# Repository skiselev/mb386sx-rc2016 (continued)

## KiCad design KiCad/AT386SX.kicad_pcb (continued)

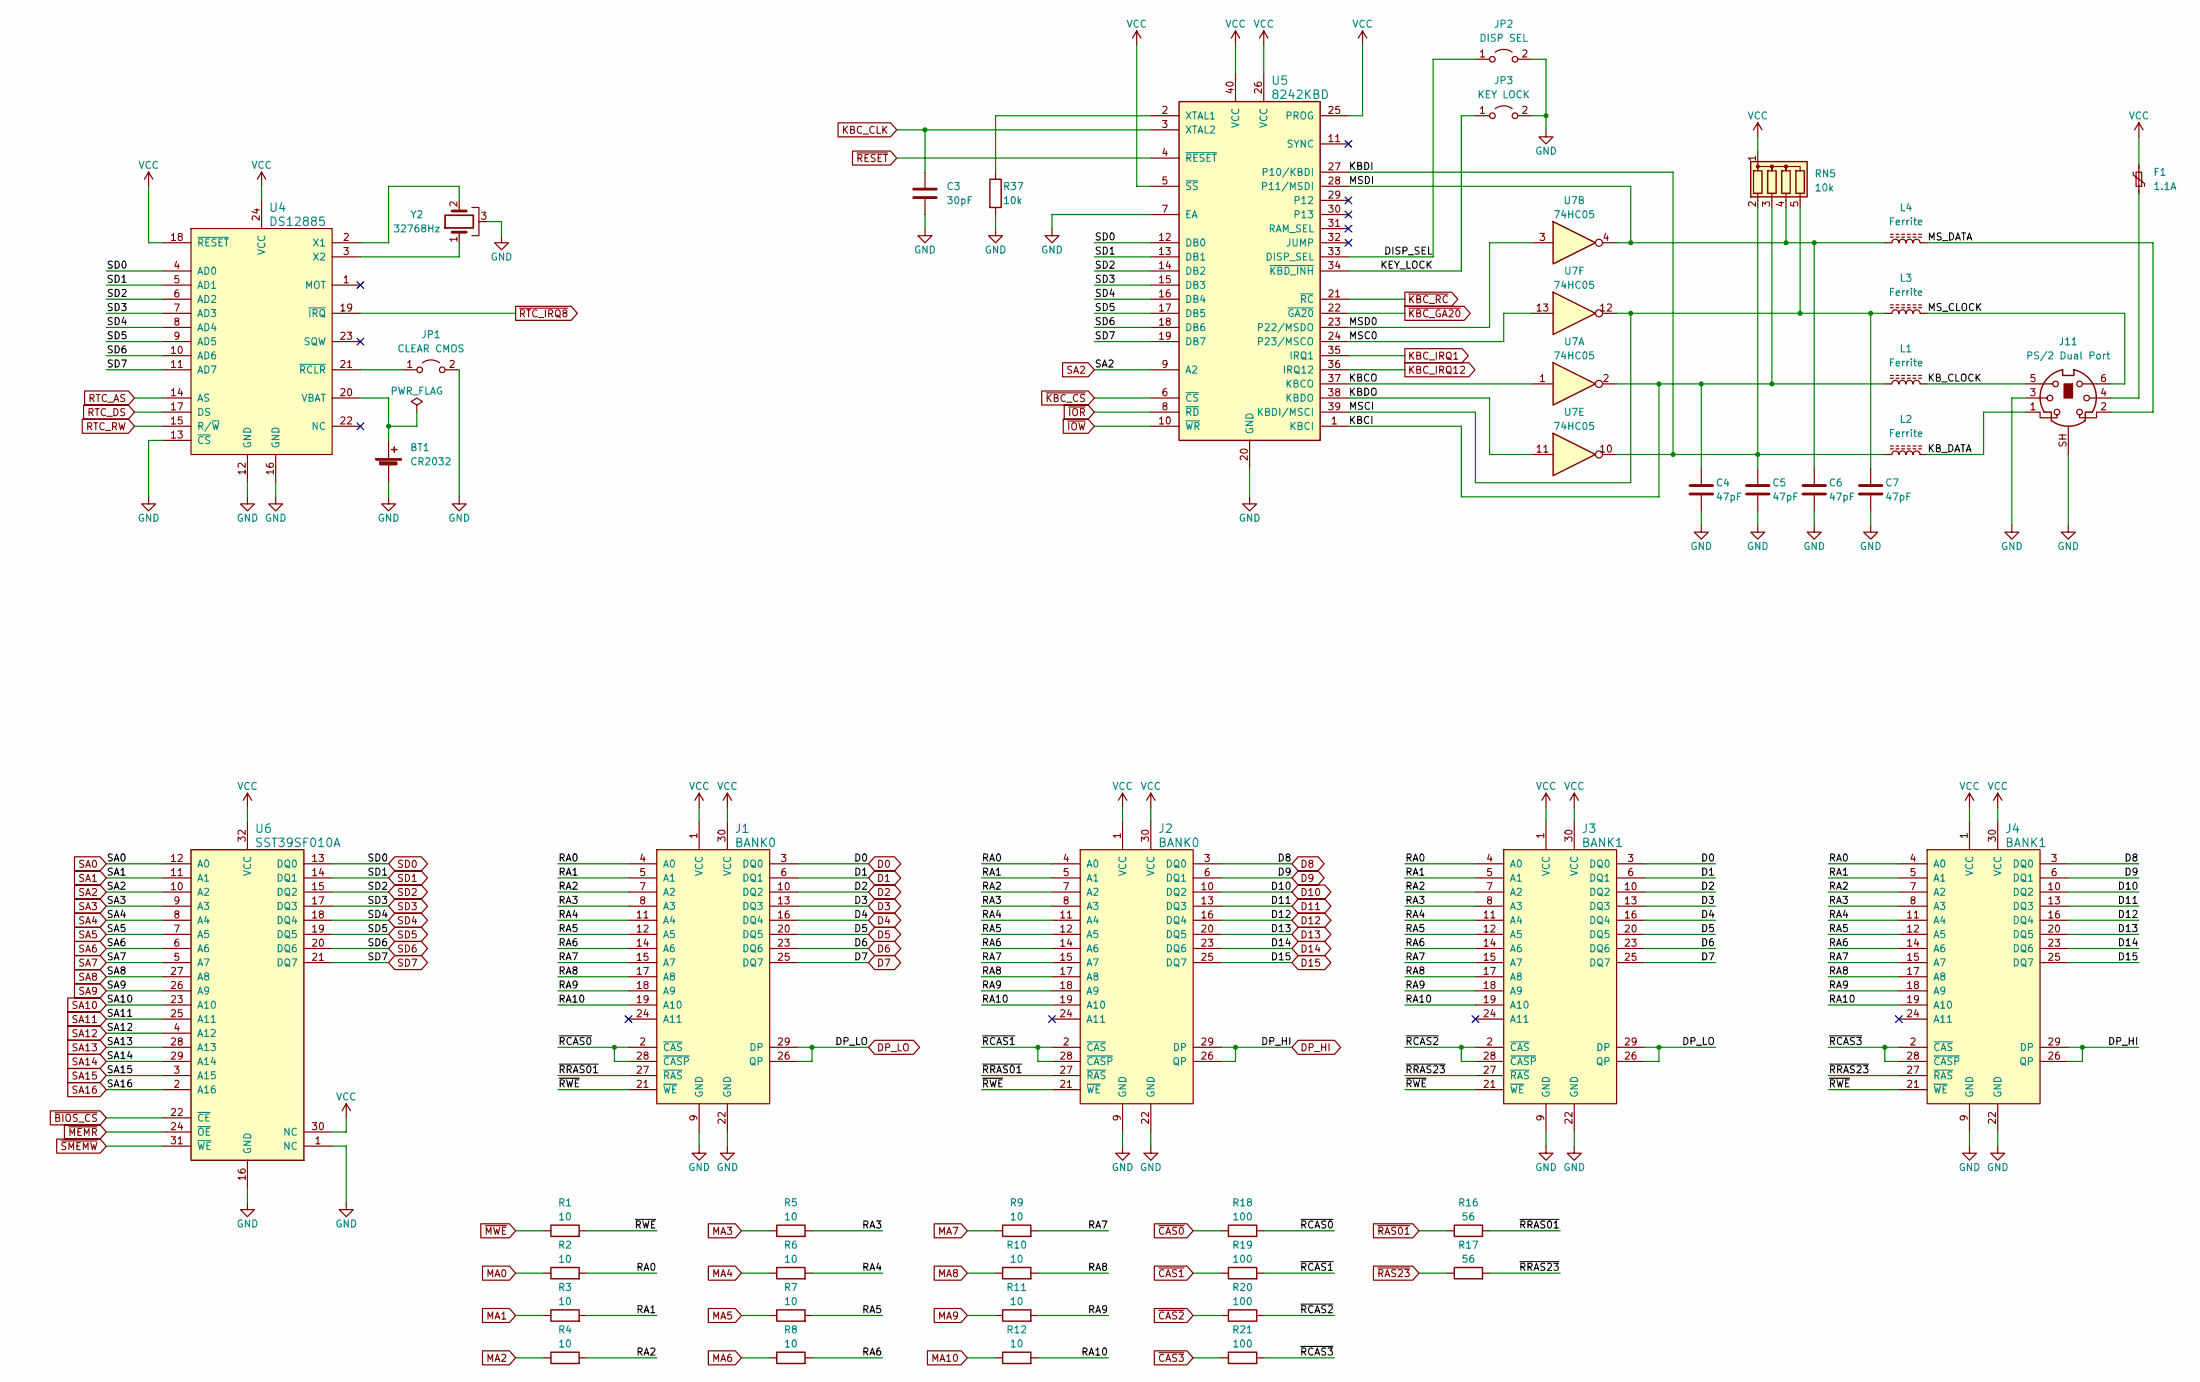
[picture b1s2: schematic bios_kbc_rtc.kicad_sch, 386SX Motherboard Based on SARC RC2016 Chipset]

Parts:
BT1: CR2032; Battery_Holder_CR2032_Universal
C3: 30pF; Cap_Cer_508
C4, C5, C6, C7: 47pF; Cap_Cer_508
F1: 1.1A; Cap_Cer_508
J1, J2: BANK0; Conn_SIMM30
J3, J4: BANK1; Conn_SIMM30
J11: PS/2 Dual Port; Conn_Mini_DIN_6pin
JP1: CLEAR CMOS; Conn_Pin_Header_2x1_2.54mm
JP2: DISP SEL; Conn_Pin_Header_2x1_2.54mm
JP3: KEY LOCK; Conn_Pin_Header_2x1_2.54mm
L1, L2, L3, L4: Ferrite; L_Ferrite_1016
R1, R2, R3, R4, R5, R6, R7, R8, R9, R10, R11, R12: 10; Res_762
R16, R17: 56; Res_762
R18, R19, R20, R21: 100; Res_762
R37: 10k; Res_762
RN5: 10k; Conn_SIL5
U4: DS12885; IC_DIP24_600
U5: 8242KBD; IC_DIP40_600
U6: SST39SF010A; IC_DIP32_600
U7: 74HC05; IC_DIP14_300
Y2: 32768Hz; Crystal_32K_Horiz

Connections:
/Memory, BIOS, Keyboard, RTC/DISP_SEL: JP2.1 (A), U5.33 (DISP_SEL)
/Memory, BIOS, Keyboard, RTC/KBCI: C4.1, L1.1, RN5.3 (R2), U5.1 (KBCI), U7.2
/Memory, BIOS, Keyboard, RTC/KBCO: U5.37 (KBCO), U7.1
/Memory, BIOS, Keyboard, RTC/KBDI: C5.1, L2.1, RN5.2 (R1), U5.27 (P10/KBDI), U7.10
/Memory, BIOS, Keyboard, RTC/KBDO: U5.38 (KBDO), U7.11
/Memory, BIOS, Keyboard, RTC/KB_CLOCK: J11.5, L1.2
/Memory, BIOS, Keyboard, RTC/KB_DATA: J11.1, L2.2
/Memory, BIOS, Keyboard, RTC/KEY_LOCK: JP3.1 (A), U5.34 (~KBD_INH)
/Memory, BIOS, Keyboard, RTC/MSC0: U5.24 (P23/MSCO), U7.13
/Memory, BIOS, Keyboard, RTC/MSCI: C7.1, L3.1, RN5.5 (R4), U5.39 (KBDI/MSCI), U7.12
/Memory, BIOS, Keyboard, RTC/MSD0: U5.23 (P22/MSDO), U7.3
/Memory, BIOS, Keyboard, RTC/MSDI: C6.1, L4.1, RN5.4 (R3), U5.28 (P11/MSDI), U7.4
/Memory, BIOS, Keyboard, RTC/MS_CLOCK: J11.6, L3.2
/Memory, BIOS, Keyboard, RTC/MS_DATA: J11.2, L4.2
/Memory, BIOS, Keyboard, RTC/RA0: J1.4 (A0), J2.4 (A0), J3.4 (A0), J4.4 (A0), R2.2
/Memory, BIOS, Keyboard, RTC/RA1: J1.5 (A1), J2.5 (A1), J3.5 (A1), J4.5 (A1), R3.2
/Memory, BIOS, Keyboard, RTC/RA2: J1.7 (A2), J2.7 (A2), J3.7 (A2), J4.7 (A2), R4.2
/Memory, BIOS, Keyboard, RTC/RA3: J1.8 (A3), J2.8 (A3), J3.8 (A3), J4.8 (A3), R5.2
/Memory, BIOS, Keyboard, RTC/RA4: J1.11 (A4), J2.11 (A4), J3.11 (A4), J4.11 (A4), R6.2
/Memory, BIOS, Keyboard, RTC/RA5: J1.12 (A5), J2.12 (A5), J3.12 (A5), J4.12 (A5), R7.2
/Memory, BIOS, Keyboard, RTC/RA6: J1.14 (A6), J2.14 (A6), J3.14 (A6), J4.14 (A6), R8.2
/Memory, BIOS, Keyboard, RTC/RA7: J1.15 (A7), J2.15 (A7), J3.15 (A7), J4.15 (A7), R9.2
/Memory, BIOS, Keyboard, RTC/RA8: J1.17 (A8), J2.17 (A8), J3.17 (A8), J4.17 (A8), R10.2
/Memory, BIOS, Keyboard, RTC/RA9: J1.18 (A9), J2.18 (A9), J3.18 (A9), J4.18 (A9), R11.2
/Memory, BIOS, Keyboard, RTC/RA10: J1.19 (A10), J2.19 (A10), J3.19 (A10), J4.19 (A10), R12.2
/Memory, BIOS, Keyboard, RTC/~RCAS0: J1.2 (~CAS), J1.28 (~CASP), R18.2
/Memory, BIOS, Keyboard, RTC/~RCAS1: J2.2 (~CAS), J2.28 (~CASP), R19.2
/Memory, BIOS, Keyboard, RTC/~RCAS2: J3.2 (~CAS), J3.28 (~CASP), R20.2
/Memory, BIOS, Keyboard, RTC/~RCAS3: J4.2 (~CAS), J4.28 (~CASP), R21.2
/Memory, BIOS, Keyboard, RTC/~RRAS01: J1.27 (~RAS), J2.27 (~RAS), R16.2
/Memory, BIOS, Keyboard, RTC/~RRAS23: J3.27 (~RAS), J4.27 (~RAS), R17.2
/Memory, BIOS, Keyboard, RTC/~RWE: J1.21 (~WE), J2.21 (~WE), J3.21 (~WE), J4.21 (~WE), R1.2
D0: J1.3 (DQ0), J3.3 (DQ0); also elsewhere on the board
D1: J1.6 (DQ1), J3.6 (DQ1); also elsewhere on the board
D2: J1.10 (DQ2), J3.10 (DQ2); also elsewhere on the board
D3: J1.13 (DQ3), J3.13 (DQ3); also elsewhere on the board
D4: J1.16 (DQ4), J3.16 (DQ4); also elsewhere on the board
D5: J1.20 (DQ5), J3.20 (DQ5); also elsewhere on the board
D6: J1.23 (DQ6), J3.23 (DQ6); also elsewhere on the board
D7: J1.25 (DQ7), J3.25 (DQ7); also elsewhere on the board
D8: J2.3 (DQ0), J4.3 (DQ0); also elsewhere on the board
D9: J2.6 (DQ1), J4.6 (DQ1); also elsewhere on the board
D10: J2.10 (DQ2), J4.10 (DQ2); also elsewhere on the board
D11: J2.13 (DQ3), J4.13 (DQ3); also elsewhere on the board
D12: J2.16 (DQ4), J4.16 (DQ4); also elsewhere on the board
D13: J2.20 (DQ5), J4.20 (DQ5); also elsewhere on the board
D14: J2.23 (DQ6), J4.23 (DQ6); also elsewhere on the board
D15: J2.25 (DQ7), J4.25 (DQ7); also elsewhere on the board
DP_HI: J2.26 (QP), J2.29 (DP), J4.26 (QP), J4.29 (DP); also elsewhere on the board
DP_LO: J1.26 (QP), J1.29 (DP), J3.26 (QP), J3.29 (DP); also elsewhere on the board
GND: BT1.2 (-), C3.2, C4.2, C5.2, C6.2, C7.2, J1.9 (GND), J1.22 (GND), J2.9 (GND), J2.22 (GND), J3.9 (GND), J3.22 (GND), J4.9 (GND), J4.22 (GND), J11.3, J11.SH, JP1.2 (B), JP2.2 (B), JP3.2 (B), R37.2, U4.12 (GND), U4.13 (~CS), U4.16 (GND), U5.7 (EA), U5.20 (GND), U6.1 (NC), U6.16 (GND), Y2.3; also elsewhere on the board
KBC_CLK: C3.1, U5.3 (XTAL2); also elsewhere on the board
KBC_IRQ1: U5.35 (IRQ1); also elsewhere on the board
KBC_IRQ12: U5.36 (IRQ12); also elsewhere on the board
MA0: R2.1; also elsewhere on the board
MA1: R3.1; also elsewhere on the board
MA2: R4.1; also elsewhere on the board
MA3: R5.1; also elsewhere on the board
MA4: R6.1; also elsewhere on the board
MA5: R7.1; also elsewhere on the board
MA6: R8.1; also elsewhere on the board
MA7: R9.1; also elsewhere on the board
MA8: R10.1; also elsewhere on the board
MA9: R11.1; also elsewhere on the board
MA10: R12.1; also elsewhere on the board
unnamed: BT1.1 (+), U4.20 (VBAT)
unnamed: F1.1, J11.4
unnamed: JP1.1 (A), U4.21 (~RCLR)
unnamed: R37.1, U5.2 (XTAL1)
unnamed: U4.2 (X1), Y2.2
unnamed: U4.3 (X2), Y2.1
RTC_AS: U4.14 (AS); also elsewhere on the board
RTC_DS: U4.17 (DS); also elsewhere on the board
RTC_RW: U4.15 (R/~W); also elsewhere on the board
SA0: U6.12 (A0); also elsewhere on the board
SA1: U6.11 (A1); also elsewhere on the board
SA2: U5.9 (A2), U6.10 (A2); also elsewhere on the board
SA3: U6.9 (A3); also elsewhere on the board
SA4: U6.8 (A4); also elsewhere on the board
SA5: U6.7 (A5); also elsewhere on the board
SA6: U6.6 (A6); also elsewhere on the board
SA7: U6.5 (A7); also elsewhere on the board
SA8: U6.27 (A8); also elsewhere on the board
SA9: U6.26 (A9); also elsewhere on the board
SA10: U6.23 (A10); also elsewhere on the board
SA11: U6.25 (A11); also elsewhere on the board
SA12: U6.4 (A12); also elsewhere on the board
SA13: U6.28 (A13); also elsewhere on the board
SA14: U6.29 (A14); also elsewhere on the board
SA15: U6.3 (A15); also elsewhere on the board
SA16: U6.2 (A16); also elsewhere on the board
SD0: U4.4 (AD0), U5.12 (DB0), U6.13 (DQ0); also elsewhere on the board
SD1: U4.5 (AD1), U5.13 (DB1), U6.14 (DQ1); also elsewhere on the board
SD2: U4.6 (AD2), U5.14 (DB2), U6.15 (DQ2); also elsewhere on the board
SD3: U4.7 (AD3), U5.15 (DB3), U6.17 (DQ3); also elsewhere on the board
SD4: U4.8 (AD4), U5.16 (DB4), U6.18 (DQ4); also elsewhere on the board
SD5: U4.9 (AD5), U5.17 (DB5), U6.19 (DQ5); also elsewhere on the board
SD6: U4.10 (AD6), U5.18 (DB6), U6.20 (DQ6); also elsewhere on the board
SD7: U4.11 (AD7), U5.19 (DB7), U6.21 (DQ7); also elsewhere on the board
VCC: F1.2, J1.1 (VCC), J1.30 (VCC), J2.1 (VCC), J2.30 (VCC), J3.1 (VCC), J3.30 (VCC), J4.1 (VCC), J4.30 (VCC), RN5.1 (common), U4.18 (~RESET), U4.24 (VCC), U5.5 (~SS), U5.25 (PROG), U5.26 (VCC), U5.40 (VCC), U6.30 (NC), U6.32 (VCC); also elsewhere on the board
~BIOS_CS: U6.22 (~CE); also elsewhere on the board
~CAS0: R18.1; also elsewhere on the board
~CAS1: R19.1; also elsewhere on the board
~CAS2: R20.1; also elsewhere on the board
~CAS3: R21.1; also elsewhere on the board
~IOR: U5.8 (~RD); also elsewhere on the board
~IOW: U5.10 (~WR); also elsewhere on the board
~KBC_CS: U5.6 (~CS); also elsewhere on the board
~KBC_GA20: U5.22 (~GA20); also elsewhere on the board
~KBC_RC: U5.21 (~RC); also elsewhere on the board
~MEMR: U6.24 (~OE); also elsewhere on the board
~MWE: R1.1; also elsewhere on the board
~RAS01: R16.1; also elsewhere on the board
~RAS23: R17.1; also elsewhere on the board
~RESET: U5.4 (~RESET); also elsewhere on the board
~RTC_IRQ8: U4.19 (~IRQ); also elsewhere on the board
~SMEMW: U6.31 (~WE); also elsewhere on the board

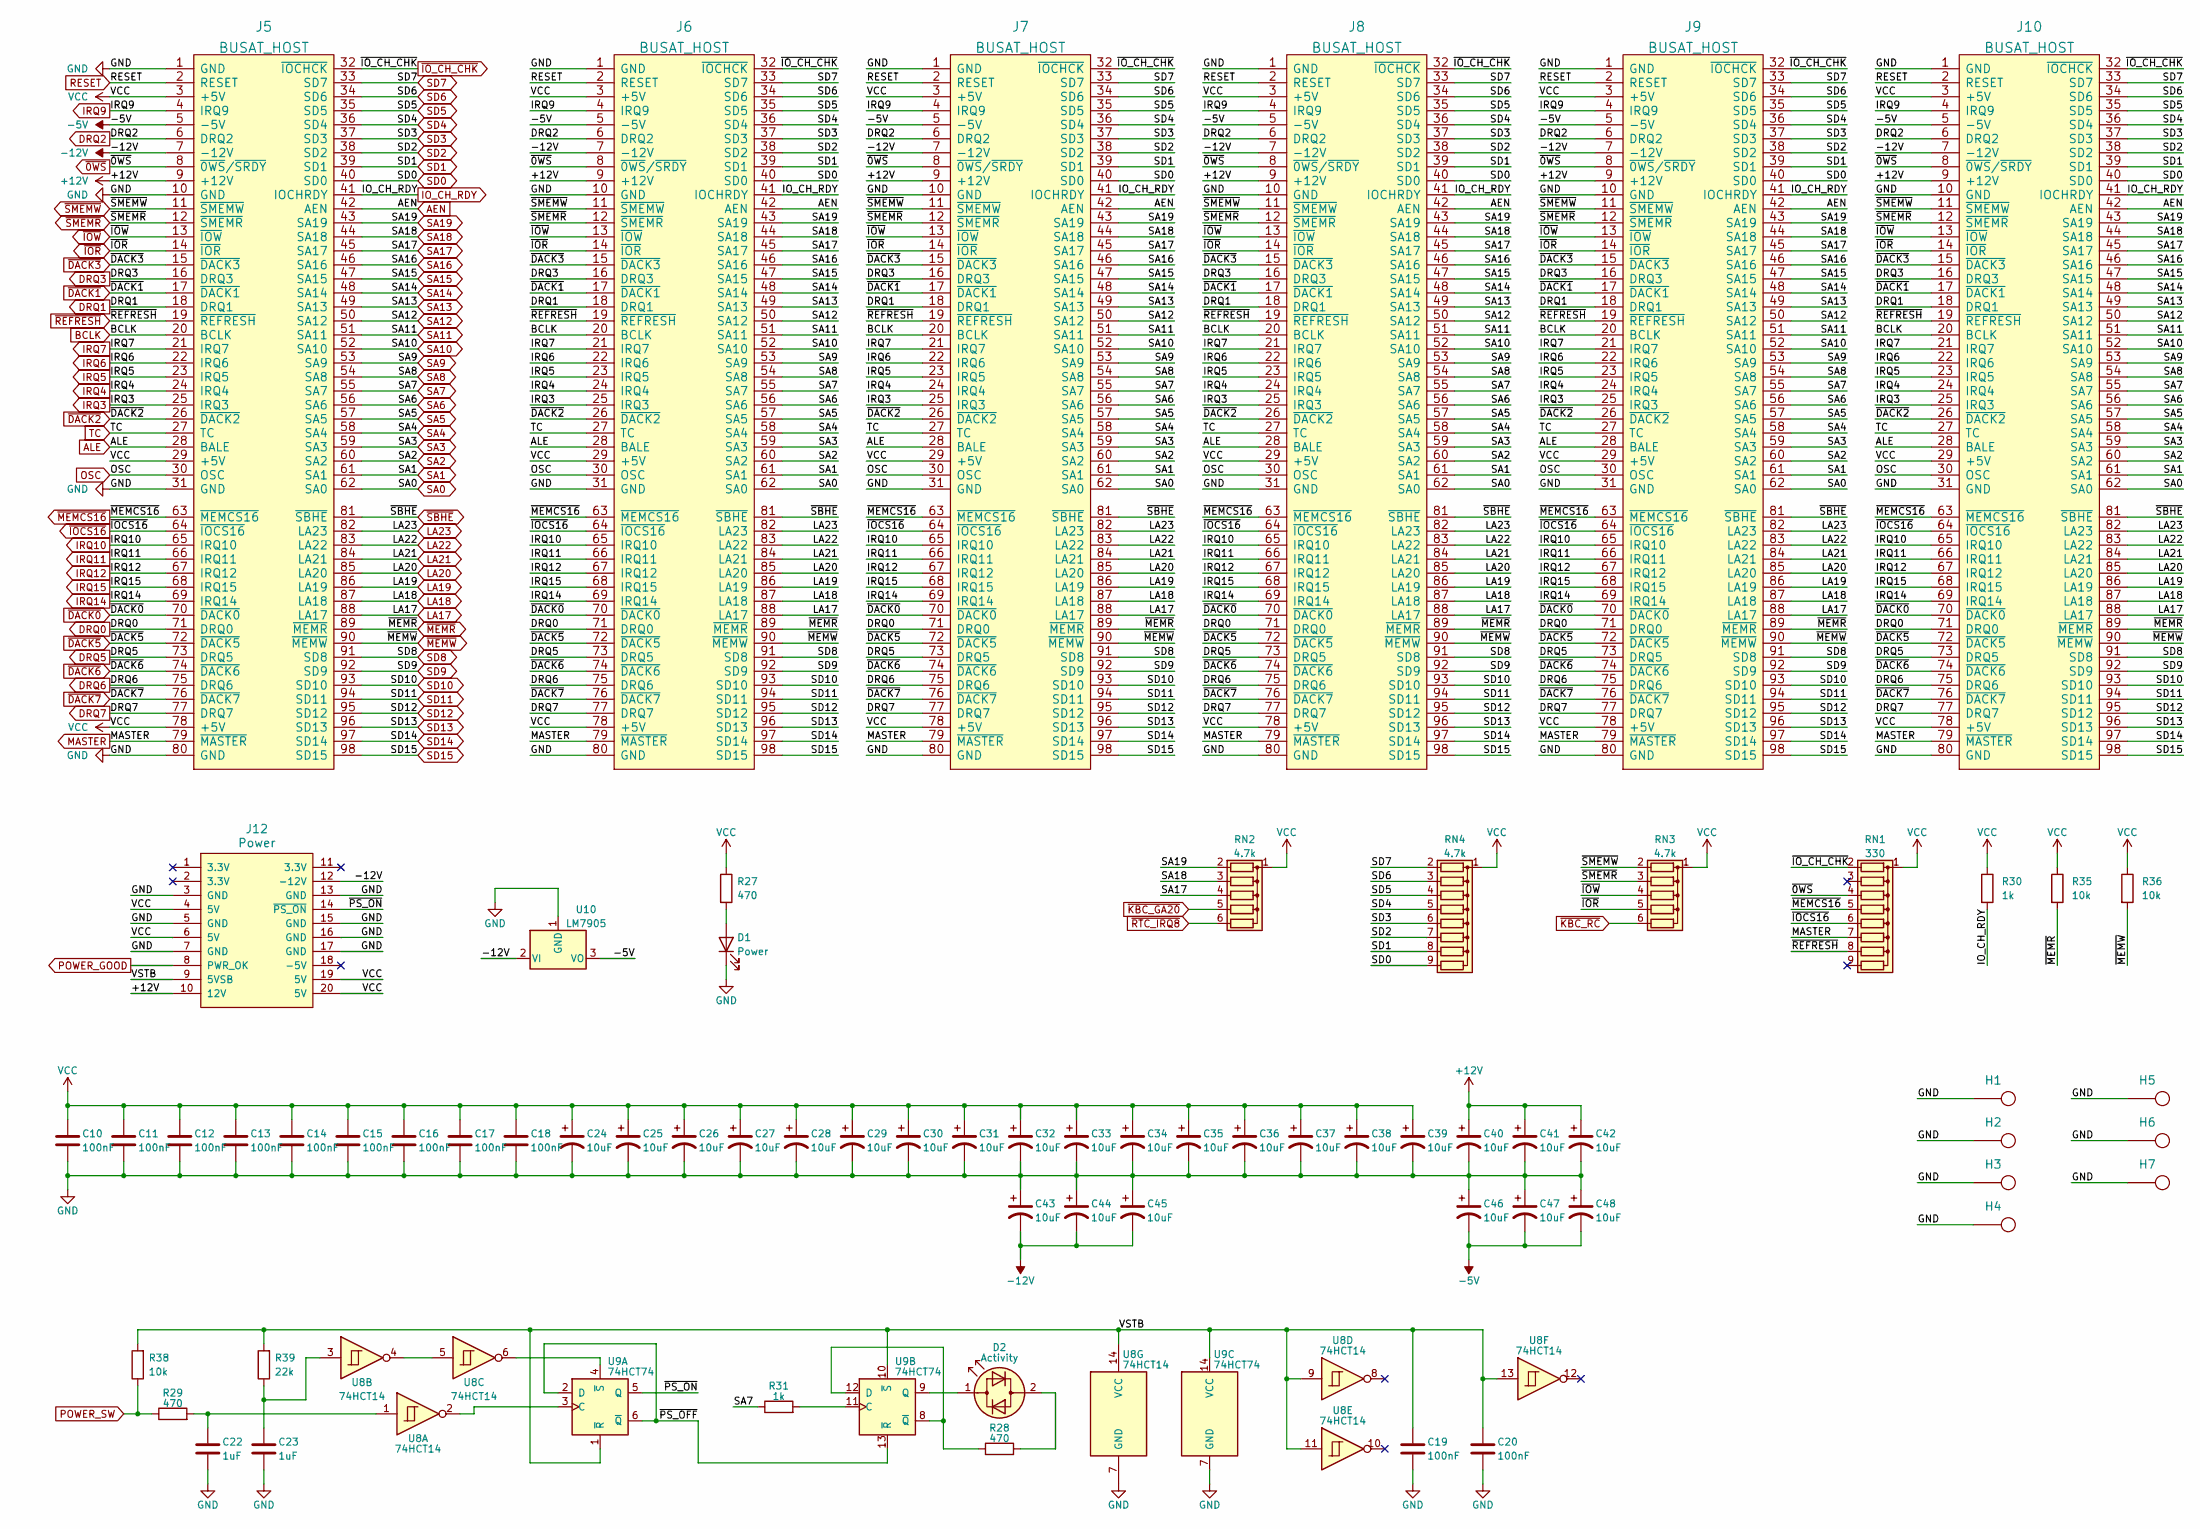
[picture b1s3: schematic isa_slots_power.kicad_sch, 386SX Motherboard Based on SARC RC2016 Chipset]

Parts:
C10, C11, C12, C13, C14, C15, C16, C17, C18, C19, C20: 100nF; Cap_Cer_508
C22, C23: 1uF; Cap_Cer_508
C24, C25, C26, C27, C28, C29, C30, C31, C32, C33, C34, C35, C36, C37, C38, C39, C40, C41, C42, C43, C44, C45, C46, C47, C48: 10uF; Cap_Elec_Radial_5mm_2.5mm
D1: Power; LED_3mm
D2: Activity; LED_3mm
H1, H2, H3, H4, H5, H6, H7: HOLE; MountingHole_4mm_Pad_Via
J5, J6, J7, J8, J9, J10: BUSAT_HOST; Conn_Edge_ISA16
J12: Power; Conn_Power_ATX_20pin
R27, R28, R29: 470; Res_762
R30, R31: 1k; Res_762
R35, R36, R38: 10k; Res_762
R39: 22k; Res_762
RN1: 330; Conn_SIL9
RN2, RN3: 4.7k; Conn_SIL6
RN4: 4.7k; Conn_SIL9
U8: 74HCT14; IC_DIP14_300
U9: 74HCT74; IC_DIP14_300
U10: LM7905; IC_TO220-3_Vert

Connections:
+12V: C40.1, C41.1, C42.1, J5.9 (+12V), J6.9 (+12V), J7.9 (+12V), J8.9 (+12V), J9.9 (+12V), J10.9 (+12V), J12.10 (12V)
-5V: C46.2, C47.2, C48.2, J5.5 (-5V), J6.5 (-5V), J7.5 (-5V), J8.5 (-5V), J9.5 (-5V), J10.5 (-5V), U10.3 (VO)
-12V: C43.2, C44.2, C45.2, J5.7 (-12V), J6.7 (-12V), J7.7 (-12V), J8.7 (-12V), J9.7 (-12V), J10.7 (-12V), J12.12 (-12V), U10.2 (VI)
/ISA Slots and Power/VSTB: C19.1, C20.1, J12.9 (5VSB), R38.2, R39.2, U8.9, U8.11, U8.13, U8.14 (VCC), U9.1 (~R), U9.10 (~S), U9.14 (VCC)
/ISA Slots and Power/~PS_OFF: U9.2 (D), U9.6 (~Q), U9.13 (~R)
/ISA Slots and Power/~PS_ON: J12.14 (~PS_ON), U9.5 (Q)
AEN: J5.42 (AEN), J6.42 (AEN), J7.42 (AEN), J8.42 (AEN), J9.42 (AEN), J10.42 (AEN); also elsewhere on the board
ALE: J5.28 (BALE), J6.28 (BALE), J7.28 (BALE), J8.28 (BALE), J9.28 (BALE), J10.28 (BALE); also elsewhere on the board
BCLK: J5.20 (BCLK), J6.20 (BCLK), J7.20 (BCLK), J8.20 (BCLK), J9.20 (BCLK), J10.20 (BCLK); also elsewhere on the board
DRQ0: J5.71 (DRQ0), J6.71 (DRQ0), J7.71 (DRQ0), J8.71 (DRQ0), J9.71 (DRQ0), J10.71 (DRQ0); also elsewhere on the board
DRQ1: J5.18 (DRQ1), J6.18 (DRQ1), J7.18 (DRQ1), J8.18 (DRQ1), J9.18 (DRQ1), J10.18 (DRQ1); also elsewhere on the board
DRQ2: J5.6 (DRQ2), J6.6 (DRQ2), J7.6 (DRQ2), J8.6 (DRQ2), J9.6 (DRQ2), J10.6 (DRQ2); also elsewhere on the board
DRQ3: J5.16 (DRQ3), J6.16 (DRQ3), J7.16 (DRQ3), J8.16 (DRQ3), J9.16 (DRQ3), J10.16 (DRQ3); also elsewhere on the board
DRQ5: J5.73 (DRQ5), J6.73 (DRQ5), J7.73 (DRQ5), J8.73 (DRQ5), J9.73 (DRQ5), J10.73 (DRQ5); also elsewhere on the board
DRQ6: J5.75 (DRQ6), J6.75 (DRQ6), J7.75 (DRQ6), J8.75 (DRQ6), J9.75 (DRQ6), J10.75 (DRQ6); also elsewhere on the board
DRQ7: J5.77 (DRQ7), J6.77 (DRQ7), J7.77 (DRQ7), J8.77 (DRQ7), J9.77 (DRQ7), J10.77 (DRQ7); also elsewhere on the board
GND: C10.2, C11.2, C12.2, C13.2, C14.2, C15.2, C16.2, C17.2, C18.2, C19.2, C20.2, C22.2, C23.2, C24.2, C25.2, C26.2, C27.2, C28.2, C29.2, C30.2, C31.2, C32.2, C33.2, C34.2, C35.2, C36.2, C37.2, C38.2, C39.2, C40.2, C41.2, C42.2, C43.1, C44.1, C45.1, C46.1, C47.1, C48.1, D1.1 (K), H1.1, H2.1, H3.1, H4.1, H5.1, H6.1, H7.1, J5.1 (GND), J5.10 (GND), J5.31 (GND), J5.80 (GND), J6.1 (GND), J6.10 (GND), J6.31 (GND), J6.80 (GND), J7.1 (GND), J7.10 (GND), J7.31 (GND), J7.80 (GND), J8.1 (GND), J8.10 (GND), J8.31 (GND), J8.80 (GND), J9.1 (GND), J9.10 (GND), J9.31 (GND), J9.80 (GND), J10.1 (GND), J10.10 (GND), J10.31 (GND), J10.80 (GND), J12.3 (GND), J12.5 (GND), J12.7 (GND), J12.13 (GND), J12.15 (GND), J12.16 (GND), J12.17 (GND), U8.7 (GND), U9.7 (GND), U10.1 (GND); also elsewhere on the board
IO_CH_RDY: J5.41 (IOCHRDY), J6.41 (IOCHRDY), J7.41 (IOCHRDY), J8.41 (IOCHRDY), J9.41 (IOCHRDY), J10.41 (IOCHRDY), R30.2; also elsewhere on the board
IRQ3: J5.25 (IRQ3), J6.25 (IRQ3), J7.25 (IRQ3), J8.25 (IRQ3), J9.25 (IRQ3), J10.25 (IRQ3); also elsewhere on the board
IRQ4: J5.24 (IRQ4), J6.24 (IRQ4), J7.24 (IRQ4), J8.24 (IRQ4), J9.24 (IRQ4), J10.24 (IRQ4); also elsewhere on the board
IRQ5: J5.23 (IRQ5), J6.23 (IRQ5), J7.23 (IRQ5), J8.23 (IRQ5), J9.23 (IRQ5), J10.23 (IRQ5); also elsewhere on the board
IRQ6: J5.22 (IRQ6), J6.22 (IRQ6), J7.22 (IRQ6), J8.22 (IRQ6), J9.22 (IRQ6), J10.22 (IRQ6); also elsewhere on the board
IRQ7: J5.21 (IRQ7), J6.21 (IRQ7), J7.21 (IRQ7), J8.21 (IRQ7), J9.21 (IRQ7), J10.21 (IRQ7); also elsewhere on the board
IRQ9: J5.4 (IRQ9), J6.4 (IRQ9), J7.4 (IRQ9), J8.4 (IRQ9), J9.4 (IRQ9), J10.4 (IRQ9); also elsewhere on the board
IRQ10: J5.65 (IRQ10), J6.65 (IRQ10), J7.65 (IRQ10), J8.65 (IRQ10), J9.65 (IRQ10), J10.65 (IRQ10); also elsewhere on the board
IRQ11: J5.66 (IRQ11), J6.66 (IRQ11), J7.66 (IRQ11), J8.66 (IRQ11), J9.66 (IRQ11), J10.66 (IRQ11); also elsewhere on the board
IRQ12: J5.67 (IRQ12), J6.67 (IRQ12), J7.67 (IRQ12), J8.67 (IRQ12), J9.67 (IRQ12), J10.67 (IRQ12); also elsewhere on the board
IRQ14: J5.69 (IRQ14), J6.69 (IRQ14), J7.69 (IRQ14), J8.69 (IRQ14), J9.69 (IRQ14), J10.69 (IRQ14); also elsewhere on the board
IRQ15: J5.68 (IRQ15), J6.68 (IRQ15), J7.68 (IRQ15), J8.68 (IRQ15), J9.68 (IRQ15), J10.68 (IRQ15); also elsewhere on the board
LA17: J5.88 (LA17), J6.88 (LA17), J7.88 (LA17), J8.88 (LA17), J9.88 (LA17), J10.88 (LA17); also elsewhere on the board
LA18: J5.87 (LA18), J6.87 (LA18), J7.87 (LA18), J8.87 (LA18), J9.87 (LA18), J10.87 (LA18); also elsewhere on the board
LA19: J5.86 (LA19), J6.86 (LA19), J7.86 (LA19), J8.86 (LA19), J9.86 (LA19), J10.86 (LA19); also elsewhere on the board
LA20: J5.85 (LA20), J6.85 (LA20), J7.85 (LA20), J8.85 (LA20), J9.85 (LA20), J10.85 (LA20); also elsewhere on the board
LA21: J5.84 (LA21), J6.84 (LA21), J7.84 (LA21), J8.84 (LA21), J9.84 (LA21), J10.84 (LA21); also elsewhere on the board
LA22: J5.83 (LA22), J6.83 (LA22), J7.83 (LA22), J8.83 (LA22), J9.83 (LA22), J10.83 (LA22); also elsewhere on the board
LA23: J5.82 (LA23), J6.82 (LA23), J7.82 (LA23), J8.82 (LA23), J9.82 (LA23), J10.82 (LA23); also elsewhere on the board
MASTER: J5.79 (~MASTER), J6.79 (~MASTER), J7.79 (~MASTER), J8.79 (~MASTER), J9.79 (~MASTER), J10.79 (~MASTER), RN1.7 (R6); also elsewhere on the board
unnamed: C22.1, R29.2, U8.1
unnamed: C23.1, R39.1, U8.3
unnamed: D1.2 (A), R27.2
unnamed: D2.1 (KA), U9.9 (Q)
unnamed: D2.2 (AK), R28.2
unnamed: R28.1, U9.8 (~Q), U9.12 (D)
unnamed: R31.2, U9.11 (C)
unnamed: U8.2, U9.3 (C)
unnamed: U8.4, U8.5
unnamed: U8.6, U9.4 (~S)
OSC: J5.30 (OSC), J6.30 (OSC), J7.30 (OSC), J8.30 (OSC), J9.30 (OSC), J10.30 (OSC); also elsewhere on the board
POWER_GOOD: J12.8 (PWR_OK); also elsewhere on the board
POWER_SW: R29.1, R38.1; also elsewhere on the board
RESET: J5.2 (RESET), J6.2 (RESET), J7.2 (RESET), J8.2 (RESET), J9.2 (RESET), J10.2 (RESET); also elsewhere on the board
SA0: J5.62 (SA0), J6.62 (SA0), J7.62 (SA0), J8.62 (SA0), J9.62 (SA0), J10.62 (SA0); also elsewhere on the board
SA1: J5.61 (SA1), J6.61 (SA1), J7.61 (SA1), J8.61 (SA1), J9.61 (SA1), J10.61 (SA1); also elsewhere on the board
SA2: J5.60 (SA2), J6.60 (SA2), J7.60 (SA2), J8.60 (SA2), J9.60 (SA2), J10.60 (SA2); also elsewhere on the board
SA3: J5.59 (SA3), J6.59 (SA3), J7.59 (SA3), J8.59 (SA3), J9.59 (SA3), J10.59 (SA3); also elsewhere on the board
SA4: J5.58 (SA4), J6.58 (SA4), J7.58 (SA4), J8.58 (SA4), J9.58 (SA4), J10.58 (SA4); also elsewhere on the board
SA5: J5.57 (SA5), J6.57 (SA5), J7.57 (SA5), J8.57 (SA5), J9.57 (SA5), J10.57 (SA5); also elsewhere on the board
SA6: J5.56 (SA6), J6.56 (SA6), J7.56 (SA6), J8.56 (SA6), J9.56 (SA6), J10.56 (SA6); also elsewhere on the board
SA7: J5.55 (SA7), J6.55 (SA7), J7.55 (SA7), J8.55 (SA7), J9.55 (SA7), J10.55 (SA7), R31.1; also elsewhere on the board
SA8: J5.54 (SA8), J6.54 (SA8), J7.54 (SA8), J8.54 (SA8), J9.54 (SA8), J10.54 (SA8); also elsewhere on the board
SA9: J5.53 (SA9), J6.53 (SA9), J7.53 (SA9), J8.53 (SA9), J9.53 (SA9), J10.53 (SA9); also elsewhere on the board
SA10: J5.52 (SA10), J6.52 (SA10), J7.52 (SA10), J8.52 (SA10), J9.52 (SA10), J10.52 (SA10); also elsewhere on the board
SA11: J5.51 (SA11), J6.51 (SA11), J7.51 (SA11), J8.51 (SA11), J9.51 (SA11), J10.51 (SA11); also elsewhere on the board
SA12: J5.50 (SA12), J6.50 (SA12), J7.50 (SA12), J8.50 (SA12), J9.50 (SA12), J10.50 (SA12); also elsewhere on the board
SA13: J5.49 (SA13), J6.49 (SA13), J7.49 (SA13), J8.49 (SA13), J9.49 (SA13), J10.49 (SA13); also elsewhere on the board
SA14: J5.48 (SA14), J6.48 (SA14), J7.48 (SA14), J8.48 (SA14), J9.48 (SA14), J10.48 (SA14); also elsewhere on the board
SA15: J5.47 (SA15), J6.47 (SA15), J7.47 (SA15), J8.47 (SA15), J9.47 (SA15), J10.47 (SA15); also elsewhere on the board
SA16: J5.46 (SA16), J6.46 (SA16), J7.46 (SA16), J8.46 (SA16), J9.46 (SA16), J10.46 (SA16); also elsewhere on the board
SA17: J5.45 (SA17), J6.45 (SA17), J7.45 (SA17), J8.45 (SA17), J9.45 (SA17), J10.45 (SA17), RN2.4 (R3); also elsewhere on the board
SA18: J5.44 (SA18), J6.44 (SA18), J7.44 (SA18), J8.44 (SA18), J9.44 (SA18), J10.44 (SA18), RN2.3 (R2); also elsewhere on the board
SA19: J5.43 (SA19), J6.43 (SA19), J7.43 (SA19), J8.43 (SA19), J9.43 (SA19), J10.43 (SA19), RN2.2 (R1); also elsewhere on the board
SD0: J5.40 (SD0), J6.40 (SD0), J7.40 (SD0), J8.40 (SD0), J9.40 (SD0), J10.40 (SD0), RN4.9 (R8); also elsewhere on the board
SD1: J5.39 (SD1), J6.39 (SD1), J7.39 (SD1), J8.39 (SD1), J9.39 (SD1), J10.39 (SD1), RN4.8 (R7); also elsewhere on the board
SD2: J5.38 (SD2), J6.38 (SD2), J7.38 (SD2), J8.38 (SD2), J9.38 (SD2), J10.38 (SD2), RN4.7 (R6); also elsewhere on the board
SD3: J5.37 (SD3), J6.37 (SD3), J7.37 (SD3), J8.37 (SD3), J9.37 (SD3), J10.37 (SD3), RN4.6 (R5); also elsewhere on the board
SD4: J5.36 (SD4), J6.36 (SD4), J7.36 (SD4), J8.36 (SD4), J9.36 (SD4), J10.36 (SD4), RN4.5 (R4); also elsewhere on the board
SD5: J5.35 (SD5), J6.35 (SD5), J7.35 (SD5), J8.35 (SD5), J9.35 (SD5), J10.35 (SD5), RN4.4 (R3); also elsewhere on the board
SD6: J5.34 (SD6), J6.34 (SD6), J7.34 (SD6), J8.34 (SD6), J9.34 (SD6), J10.34 (SD6), RN4.3 (R2); also elsewhere on the board
SD7: J5.33 (SD7), J6.33 (SD7), J7.33 (SD7), J8.33 (SD7), J9.33 (SD7), J10.33 (SD7), RN4.2 (R1); also elsewhere on the board
SD8: J5.91 (SD8), J6.91 (SD8), J7.91 (SD8), J8.91 (SD8), J9.91 (SD8), J10.91 (SD8); also elsewhere on the board
SD9: J5.92 (SD9), J6.92 (SD9), J7.92 (SD9), J8.92 (SD9), J9.92 (SD9), J10.92 (SD9); also elsewhere on the board
SD10: J5.93 (SD10), J6.93 (SD10), J7.93 (SD10), J8.93 (SD10), J9.93 (SD10), J10.93 (SD10); also elsewhere on the board
SD11: J5.94 (SD11), J6.94 (SD11), J7.94 (SD11), J8.94 (SD11), J9.94 (SD11), J10.94 (SD11); also elsewhere on the board
SD12: J5.95 (SD12), J6.95 (SD12), J7.95 (SD12), J8.95 (SD12), J9.95 (SD12), J10.95 (SD12); also elsewhere on the board
SD13: J5.96 (SD13), J6.96 (SD13), J7.96 (SD13), J8.96 (SD13), J9.96 (SD13), J10.96 (SD13); also elsewhere on the board
SD14: J5.97 (SD14), J6.97 (SD14), J7.97 (SD14), J8.97 (SD14), J9.97 (SD14), J10.97 (SD14); also elsewhere on the board
SD15: J5.98 (SD15), J6.98 (SD15), J7.98 (SD15), J8.98 (SD15), J9.98 (SD15), J10.98 (SD15); also elsewhere on the board
TC: J5.27 (TC), J6.27 (TC), J7.27 (TC), J8.27 (TC), J9.27 (TC), J10.27 (TC); also elsewhere on the board
VCC: C10.1, C11.1, C12.1, C13.1, C14.1, C15.1, C16.1, C17.1, C18.1, C24.1, C25.1, C26.1, C27.1, C28.1, C29.1, C30.1, C31.1, C32.1, C33.1, C34.1, C35.1, C36.1, C37.1, C38.1, C39.1, J5.3 (+5V), J5.29 (+5V), J5.78 (+5V), J6.3 (+5V), J6.29 (+5V), J6.78 (+5V), J7.3 (+5V), J7.29 (+5V), J7.78 (+5V), J8.3 (+5V), J8.29 (+5V), J8.78 (+5V), J9.3 (+5V), J9.29 (+5V), J9.78 (+5V), J10.3 (+5V), J10.29 (+5V), J10.78 (+5V), J12.4 (5V), J12.6 (5V), J12.19 (5V), J12.20 (5V), R27.1, R30.1, R35.1, R36.1, RN1.1 (common), RN2.1 (common), RN3.1 (common), RN4.1 (common); also elsewhere on the board
~0WS: J5.8 (~0WS/~SRDY), J6.8 (~0WS/~SRDY), J7.8 (~0WS/~SRDY), J8.8 (~0WS/~SRDY), J9.8 (~0WS/~SRDY), J10.8 (~0WS/~SRDY), RN1.4 (R3); also elsewhere on the board
~DACK0: J5.70 (~DACK0), J6.70 (~DACK0), J7.70 (~DACK0), J8.70 (~DACK0), J9.70 (~DACK0), J10.70 (~DACK0); also elsewhere on the board
~DACK1: J5.17 (~DACK1), J6.17 (~DACK1), J7.17 (~DACK1), J8.17 (~DACK1), J9.17 (~DACK1), J10.17 (~DACK1); also elsewhere on the board
~DACK2: J5.26 (~DACK2), J6.26 (~DACK2), J7.26 (~DACK2), J8.26 (~DACK2), J9.26 (~DACK2), J10.26 (~DACK2); also elsewhere on the board
~DACK3: J5.15 (~DACK3), J6.15 (~DACK3), J7.15 (~DACK3), J8.15 (~DACK3), J9.15 (~DACK3), J10.15 (~DACK3); also elsewhere on the board
~DACK5: J5.72 (~DACK5), J6.72 (~DACK5), J7.72 (~DACK5), J8.72 (~DACK5), J9.72 (~DACK5), J10.72 (~DACK5); also elsewhere on the board
~DACK6: J5.74 (~DACK6), J6.74 (~DACK6), J7.74 (~DACK6), J8.74 (~DACK6), J9.74 (~DACK6), J10.74 (~DACK6); also elsewhere on the board
~DACK7: J5.76 (~DACK7), J6.76 (~DACK7), J7.76 (~DACK7), J8.76 (~DACK7), J9.76 (~DACK7), J10.76 (~DACK7); also elsewhere on the board
~IOCS16: J5.64 (~IOCS16), J6.64 (~IOCS16), J7.64 (~IOCS16), J8.64 (~IOCS16), J9.64 (~IOCS16), J10.64 (~IOCS16), RN1.6 (R5); also elsewhere on the board
~IOR: J5.14 (~IOR), J6.14 (~IOR), J7.14 (~IOR), J8.14 (~IOR), J9.14 (~IOR), J10.14 (~IOR), RN3.5 (R4); also elsewhere on the board
~IOW: J5.13 (~IOW), J6.13 (~IOW), J7.13 (~IOW), J8.13 (~IOW), J9.13 (~IOW), J10.13 (~IOW), RN3.4 (R3); also elsewhere on the board
~IO_CH_CHK: J5.32 (~IOCHCK), J6.32 (~IOCHCK), J7.32 (~IOCHCK), J8.32 (~IOCHCK), J9.32 (~IOCHCK), J10.32 (~IOCHCK), RN1.2 (R1); also elsewhere on the board
~KBC_GA20: RN2.5 (R4); also elsewhere on the board
~KBC_RC: RN3.6 (R5); also elsewhere on the board
~MEMCS16: J5.63 (~MEMCS16), J6.63 (~MEMCS16), J7.63 (~MEMCS16), J8.63 (~MEMCS16), J9.63 (~MEMCS16), J10.63 (~MEMCS16), RN1.5 (R4); also elsewhere on the board
~MEMR: J5.89 (~MEMR), J6.89 (~MEMR), J7.89 (~MEMR), J8.89 (~MEMR), J9.89 (~MEMR), J10.89 (~MEMR), R35.2; also elsewhere on the board
~MEMW: J5.90 (~MEMW), J6.90 (~MEMW), J7.90 (~MEMW), J8.90 (~MEMW), J9.90 (~MEMW), J10.90 (~MEMW), R36.2; also elsewhere on the board
~REFRESH: J5.19 (~REFRESH), J6.19 (~REFRESH), J7.19 (~REFRESH), J8.19 (~REFRESH), J9.19 (~REFRESH), J10.19 (~REFRESH), RN1.8 (R7); also elsewhere on the board
~RTC_IRQ8: RN2.6 (R5); also elsewhere on the board
~SBHE: J5.81 (~SBHE), J6.81 (~SBHE), J7.81 (~SBHE), J8.81 (~SBHE), J9.81 (~SBHE), J10.81 (~SBHE); also elsewhere on the board
~SMEMR: J5.12 (~SMEMR), J6.12 (~SMEMR), J7.12 (~SMEMR), J8.12 (~SMEMR), J9.12 (~SMEMR), J10.12 (~SMEMR), RN3.3 (R2); also elsewhere on the board
~SMEMW: J5.11 (~SMEMW), J6.11 (~SMEMW), J7.11 (~SMEMW), J8.11 (~SMEMW), J9.11 (~SMEMW), J10.11 (~SMEMW), RN3.2 (R1); also elsewhere on the board

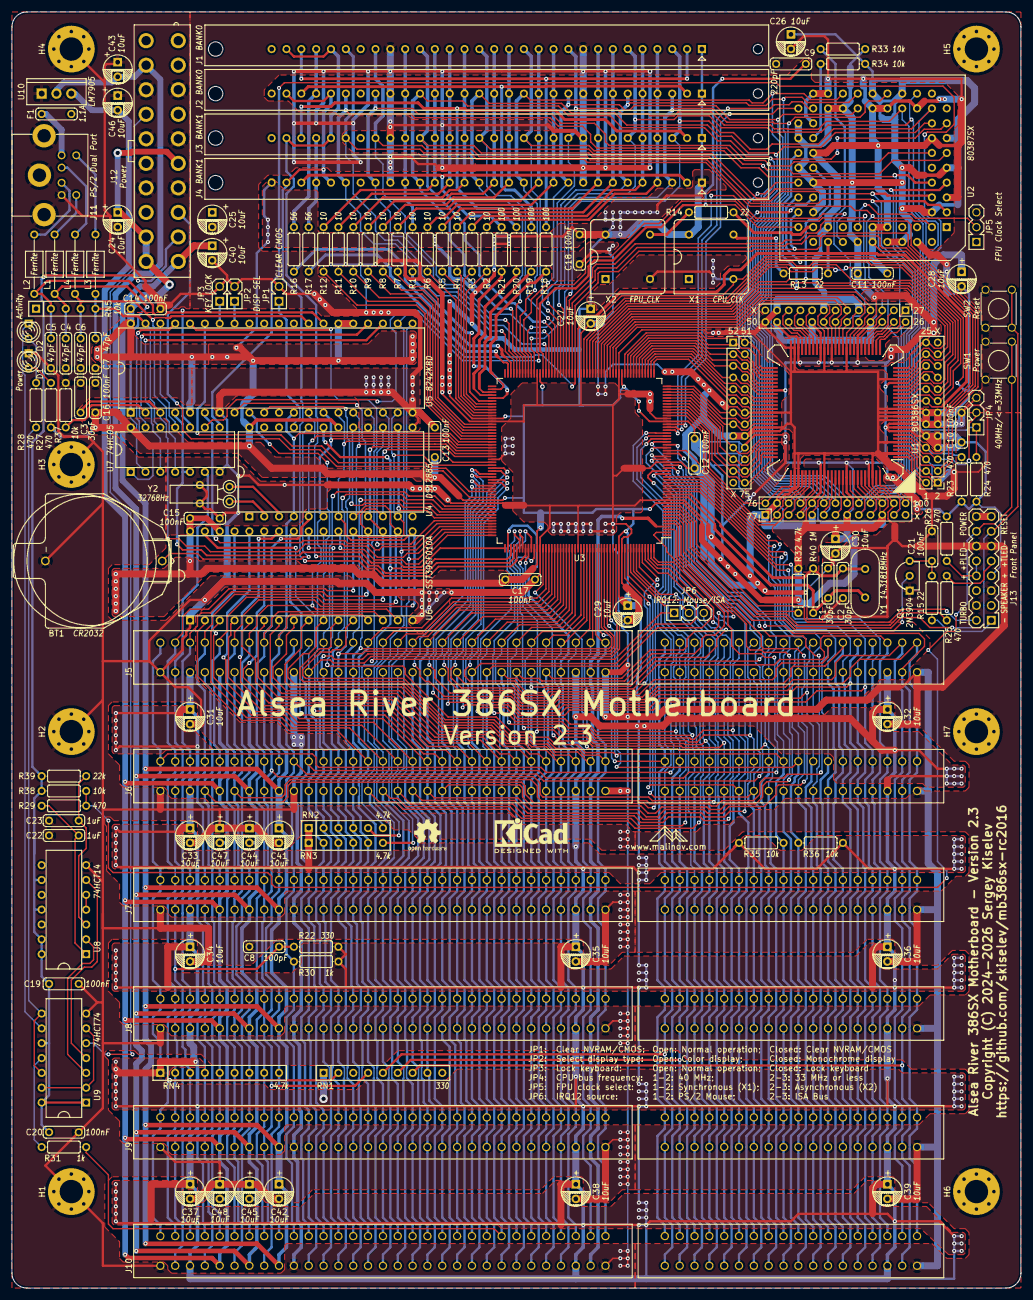
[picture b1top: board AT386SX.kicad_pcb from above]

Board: 2 copper layers, 172.7 x 218.4 mm, 150 parts (0 on the bottom side), 267 nets.

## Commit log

2024-03-01 Add KiCad files for version 1.0
2024-03-01 Add R32, update footprints
2024-03-02 Add wishlist to the readme
2024-03-02 Use DS12885 RTC
2024-03-03 Add support for 128 KiB Flash ROM ICs
2024-03-05 Version 1.3: Implement PS/2 mouse. Use PS/2 dualport pinout for the keyboard/mouse connector
2024-03-05 Version 1.4: Move mounting holes to ATX compatible locations
2024-03-06 Version 1.5: Add filtering capacitors
2024-03-08 Version 1.6: Use half-can oscillators and low-profile crystal
2024-03-21 Version 1.7: Use single front panel connector
2024-04-23 Connect /OE and /WE of the BIOS ROM to allow Flash ROM in-system programming; Rotate the PCB into portrait orientation
2026-01-10 Version 1.9: Add pin headers for the CPU
2026-01-10 README: Add changes for versions 1.8 and 1.9
2026-01-14 Update zones and tracks, relocate components near the front panel header
2026-01-14 Fix DRCs
2026-01-28 Use ATX power supply, add ATX power-on circuit
2026-01-28 README: Changes for Version 2.0
2026-01-28 Version 2.1: Reorder component references; Update silkscreen; Add signal names on the back silkscreen
2026-01-28 Version 2.1: Add Gerber files
2026-01-28 README: Changes for Version 2.1
2026-01-29 README: Re-arrange the changes from newest to oldest
2026-01-29 README: Add the BoM, except for the capacitors, resistors, and ferrite chokes.
2026-01-29 README: Complete the BoM
2026-01-29 README: Add Mouser part numbers
2026-02-04 README: Fix table formatting
2026-02-04 README: Fix 2 pin header part number
2026-02-13 README: Add known issues
2026-02-13 README: Update 10 uF capacitor part number. Add Status.
2026-02-18 Add a polyfuse for the PS/2 port
2026-02-18 README: Add polyfuse
2026-02-18 README: Update 32768 kHz crystal data
2026-02-19 README: Add tested CPUs list
2026-02-24 README: Add PS/2 and BIOS testing results
2026-02-24 Update BIOS for Alsea River Motherboard
    * Enable PS/2 mouse
    * Disable Power Management menu
    * Disable External Cache menu option
    * Enable Parity Check menu option
    * Update Setup Defaults:
    * CPU cache: Enabled
2026-02-24 SARC_RC2016: RAS to CAS width update
2026-02-24 SARC_RC2016: Uopdate Auto Settings Table
2026-02-25 SARC_RC2016: Add 0x80 bit 3
2026-02-25 SARC_RC2016: Add pinout
2026-02-25 README: Typo fix
2026-02-26 SARC_RC2016: Update pins 104 and 105
2026-02-26 Add version 2.3 files
2026-02-26 SARC_RC2016: Fix typo, update NC pins
2026-02-26 README: Add version 2.3 changes
2026-02-28 SARC_RC2016: Add DRAM refresh timing and ISA bus timing
2026-03-09 Update SARC_RC2016.md
    SARC_RC2016: Add info about Fast A20 Gate and Fast Reset as described [here](https://www.vogons.org/viewtopic.php?p=1409852#p1409852)
2026-03-10 README: Update links to the components on Mouser
2026-03-12 README: Version 2.3 updates
2026-03-13 SARC_RC2016: Update 0x87 bits 0,1
2026-03-13 User_Guide: Add PS/2 mouse information
2026-03-13 README: Add links to other .md files. Fix typos.
2026-03-14 User_Guide: Add LEDs and switches section, add a note about JP6 jumper for PS/2 mouse.
2026-03-14 User_Guide: Activity LED color clarification.
2026-03-30 SARC_RC2016: Update EMM registers description
2026-05-13 Add 3D printed test bench case
2026-05-13 Update 3D printed case
2026-05-13 Add STL files
